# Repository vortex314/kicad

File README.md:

my personal selection of projects and components in Kicad
ESP32
UEXT

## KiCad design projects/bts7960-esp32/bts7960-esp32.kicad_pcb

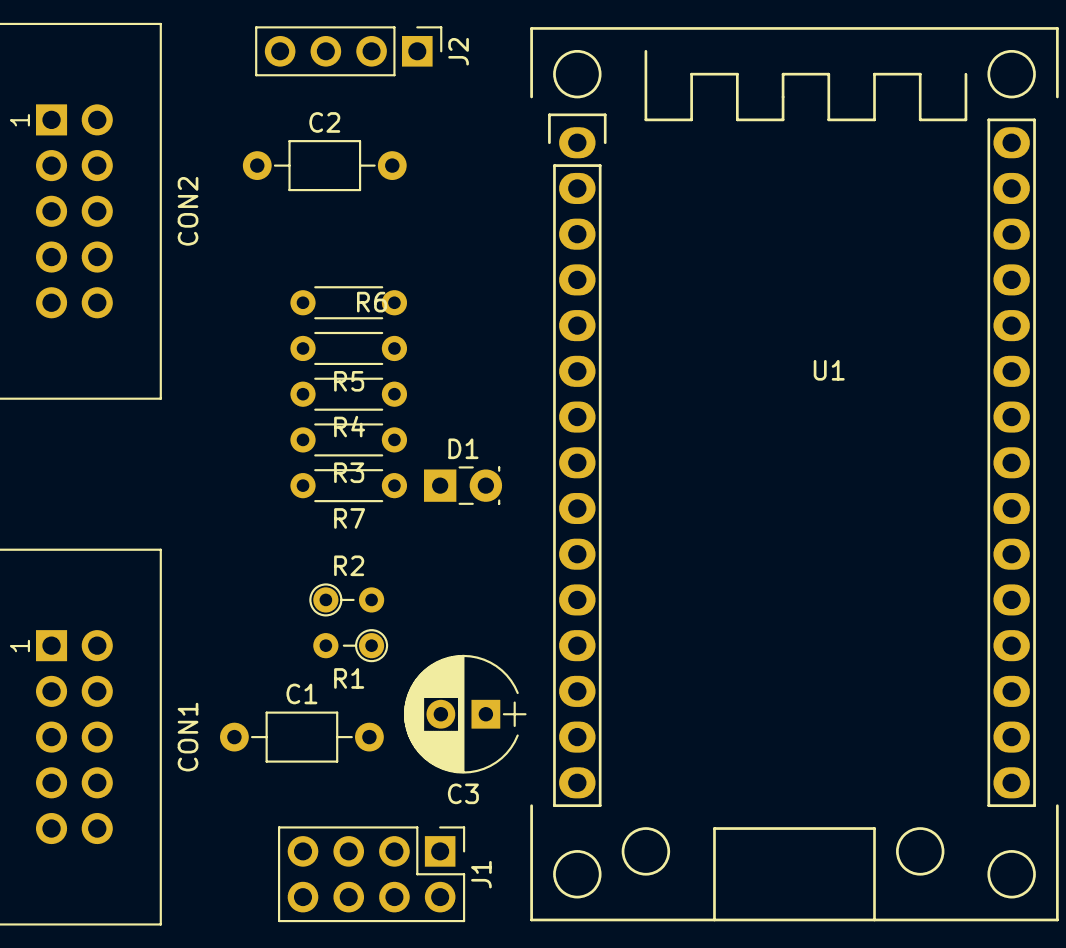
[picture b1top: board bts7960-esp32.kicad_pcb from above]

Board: 2 copper layers, 16 parts (0 on the bottom side), 23 nets, no tracks yet.

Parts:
C1, C2: 0.1µ; C_Axial_L3.8mm_D2.6mm_P7.50mm_Horizontal
C3: CP; CP_Radial_D6.3mm_P2.50mm
CON1, CON2: UEXT-5V; UEXT
D1: LED; LED_Rectangular_W3.9mm_H1.9mm
J1: CONN_02X04; Pin_Header_Straight_2x04_Pitch2.54mm
J2: CONN_01X04; Pin_Header_Straight_1x04_Pitch2.54mm
R1, R2: 10k; R_Axial_DIN0204_L3.6mm_D1.6mm_P2.54mm_Vertical
R3, R4: 10k; R_Axial_DIN0204_L3.6mm_D1.6mm_P5.08mm_Horizontal
R5, R6: 10K; R_Axial_DIN0204_L3.6mm_D1.6mm_P5.08mm_Horizontal
R7: R; R_Axial_DIN0204_L3.6mm_D1.6mm_P5.08mm_Horizontal
U1: ESP32-DEVKIT-V1

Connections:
5V: C3.1, CON1.+5V, CON2.+5V, J1.2, J2.4, R5.1, R6.1, R7.2, U1.15
CHAN_A: CON1.MISO, R4.1, U1.4
CHAN_B: CON2.MISO, R3.1, U1.5
GND: C1.2, C3.2, CON1.GND, CON2.GND, J1.1, J2.1, U1.14, U1.17
L_EN: CON1.SCL, J1.5, U1.8
L_IS: C1.1, R1.2, U1.2
L_PWM: CON1.SSEL, J1.7, U1.6
MOSI1: CON1.MOSI, U1.30
MOSI2: CON2.MOSI, U1.29
unnamed: D1.1, R7.1
unnamed: J1.3, R1.1
unnamed: J1.4, R2.2
unnamed: J2.2, R4.2, R6.2
unnamed: J2.3, R3.2, R5.2
RXD2: C2.1, CON2.RXD, R2.1, U1.3
R_EN: CON1.SDA, J1.6, U1.9
R_PWM: CON2.SSEL, J1.8, U1.7
SCK1: CON1.SCK, U1.22
SCK2: CON2.SCK, U1.21
SCL2: CON2.SCL, U1.10
SDA2: CON2.SDA, U1.11
TXD1: CON1.TXD, U1.25
TXD2: CON2.TXD, U1.24

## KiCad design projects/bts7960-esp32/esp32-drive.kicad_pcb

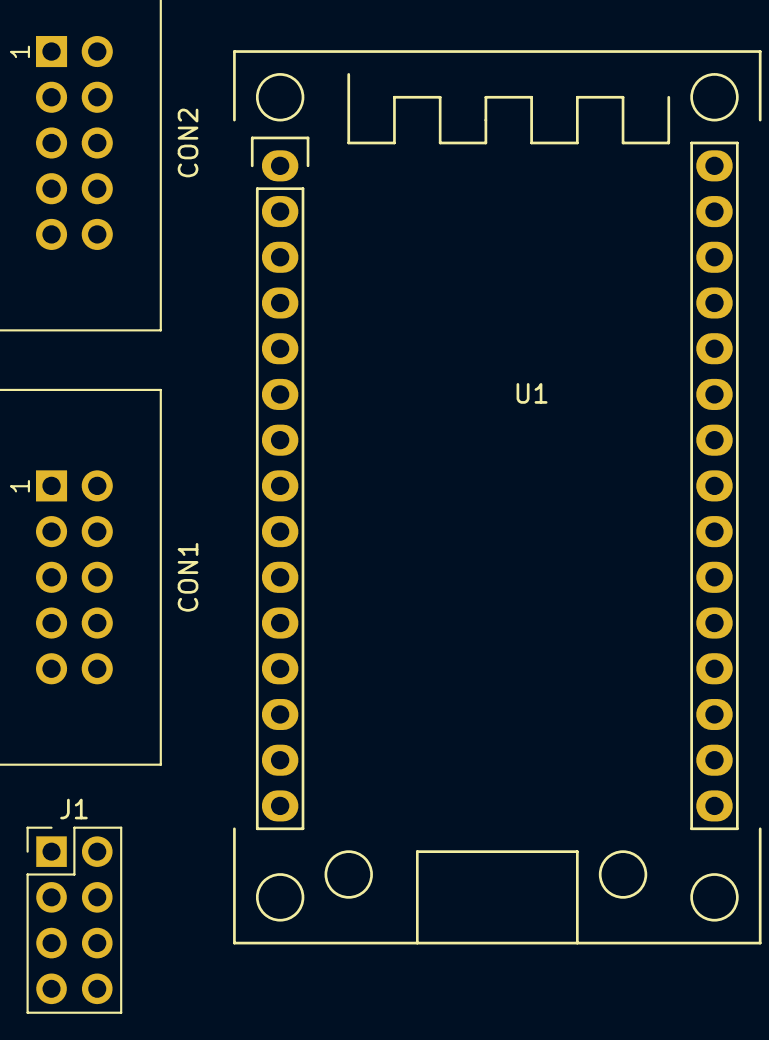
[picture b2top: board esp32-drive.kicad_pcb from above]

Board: 2 copper layers, 4 parts (0 on the bottom side), 18 nets, no tracks yet.

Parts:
CON1, CON2: UEXT
J1: CONN_02X04; Pin_Header_Straight_2x04_Pitch2.54mm
U1: ESP32-DEVKIT-V1

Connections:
5V: J1.2, U1.15
GND: CON1.GND, CON2.GND, J1.1, U1.14, U1.17
MISO1: CON1.MISO, J1.4, U1.4
MISO2: CON2.MISO, U1.5
MOSI1: CON1.MOSI, U1.29
MOSI2: CON2.MOSI, U1.30
RXD1: CON1.RXD, J1.3, U1.2
RXD2: CON2.RXD, U1.3
SCK1: CON1.SCK, U1.21
SCK2: CON2.SCK, U1.22
SCL1: CON1.SCL, J1.5, U1.8
SCL2: CON2.SCL, U1.10
SDA1: CON1.SDA, J1.6, U1.9
SDA2: CON2.SDA, U1.11
SSEL1: CON1.SSEL, J1.8, U1.7
SSEL2: CON2.SSEL, U1.6
TXD1: CON1.TXD, J1.7, U1.25
TXD2: CON2.TXD, U1.24

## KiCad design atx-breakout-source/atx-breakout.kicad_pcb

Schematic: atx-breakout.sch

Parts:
D1: LED_SB; LED-5MM
D2: LED_SW; LED-5MM
D3: LED_OK; LED-5MM
F1, F2, F3, F4, F5, F6: PTC 1.25A; C_1812_HandSoldering
J1: ATX_24PIN; Molex_MiniFit-JR-5556-24A_2x12x4.20mm_Straight
J2, J3: ATX_EPS12V; Molex_MiniFit-JR-5556-08A_2x04x4.20mm_Straight
J4, J5, J6, J7: ATX_PCIE_6PIN; Molex_MiniFit-JR-5556-06A_2x03x4.20mm_Straight_PCIE_6p2
JP1, JP2, JP3: JUMPER3; GND_JMP
JP4: JUMPER; 12V_JMP
P1, P2: CONN_01X01; SolderWirePad_single_0-8mmDrill
P3: CONN_MISC; Socket_Strip_Straight_2x08
P4: CONN_12V_1; TerminalBlock_Pheonix_PT-5.0mm_6pol
P5: CONN_12V_2; TerminalBlock_Pheonix_PT-5.0mm_6pol
P6: CONN_3V3; TerminalBlock_Pheonix_PT-5.0mm_4pol
P7: CONN_5V; TerminalBlock_Pheonix_PT-5.0mm_4pol
R1, R2, R3: 470; Resistor_Horizontal_RM10mm
SW1: SPDT; SW_SPDT_OS102011MS2Q
U1: LOGIC_BUFFER_3ST; SOT-23-5

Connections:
+3V3: F4.2, J1.1 (+3.3V), J1.2 (+3.3V), J1.12 (+3.3V), J1.13 (+3.3V), P6.2, P6.4
+5V: F5.2, J1.4 (+5V), J1.6 (+5V), J1.21 (+5V), J1.22 (+5V), J1.23 (+5V), P7.1, P7.3
+5VSB: D1.2 (A), D2.2 (A), F1.2, J1.9 (+5VSB), U1.5 (VCC)
+12V: F6.2, J1.10 (+12V1), J1.11 (+12V1), J2.5 (+12V), J2.6 (+12V), J2.7 (+12V), J2.8 (+12V), J3.5 (+12V), J3.6 (+12V), J3.7 (+12V), J3.8 (+12V), J4.1 (+12V), J4.2 (+12V), J4.3 (+12V), J5.1 (+12V), J5.2 (+12V), J5.3 (+12V), J6.1 (+12V), J6.2 (+12V), J6.3 (+12V), J7.1 (+12V), J7.2 (+12V), J7.3 (+12V), JP4.1, JP4.2, P4.2, P4.4, P4.6, P5.1, P5.3, P5.5
-5V: F3.2, J1.20 (-5V?)
-12V: F2.2, J1.14 (-12V)
GND: J1.3 (COM), J1.5 (COM), J1.7 (COM), J1.15 (COM), J1.17 (COM), J1.18 (COM), J1.19 (COM), J1.24 (COM), J2.1 (GND), J2.2 (GND), J2.3 (GND), J2.4 (GND), J3.1 (GND), J3.2 (GND), J3.3 (GND), J3.4 (GND), J4.4 (GND), J4.5 (GND), J4.6 (GND), J5.4 (GND), J5.5 (GND), J5.6 (GND), J6.4 (GND), J6.5 (GND), J6.6 (GND), J7.4 (GND), J7.5 (GND), J7.6 (GND), JP1.1, JP1.2, JP1.3, JP2.1, JP2.2, JP2.3, JP3.1, JP3.2, JP3.3, P3.2, P3.4, P3.6, P3.8, P3.10, P3.12, P3.14, P3.16, P4.1, P4.3, P4.5, P5.2, P5.4, P5.6, P6.1, P6.3, P7.2, P7.4, R1.1, R3.1, SW1.2, SW1.3, U1.1 (~OE), U1.3 (GND)
unnamed: D1.1 (K), R1.2
unnamed: D2.1 (K), R2.2
unnamed: D3.1 (K), R3.2
unnamed: F1.1, P3.15
unnamed: F2.1, P3.9
unnamed: F3.1, P3.7
unnamed: F4.1, P3.5
unnamed: F5.1, P3.3
unnamed: F6.1, P3.1
PS_ON: J1.16 (PS_ON), P3.13, R2.1, SW1.1
PWR_OK_BUF: D3.2 (A), P2.1, P3.11, U1.4 (Y)
PWR_OK_RAW: J1.8 (PWROK), P1.1, U1.2 (A)

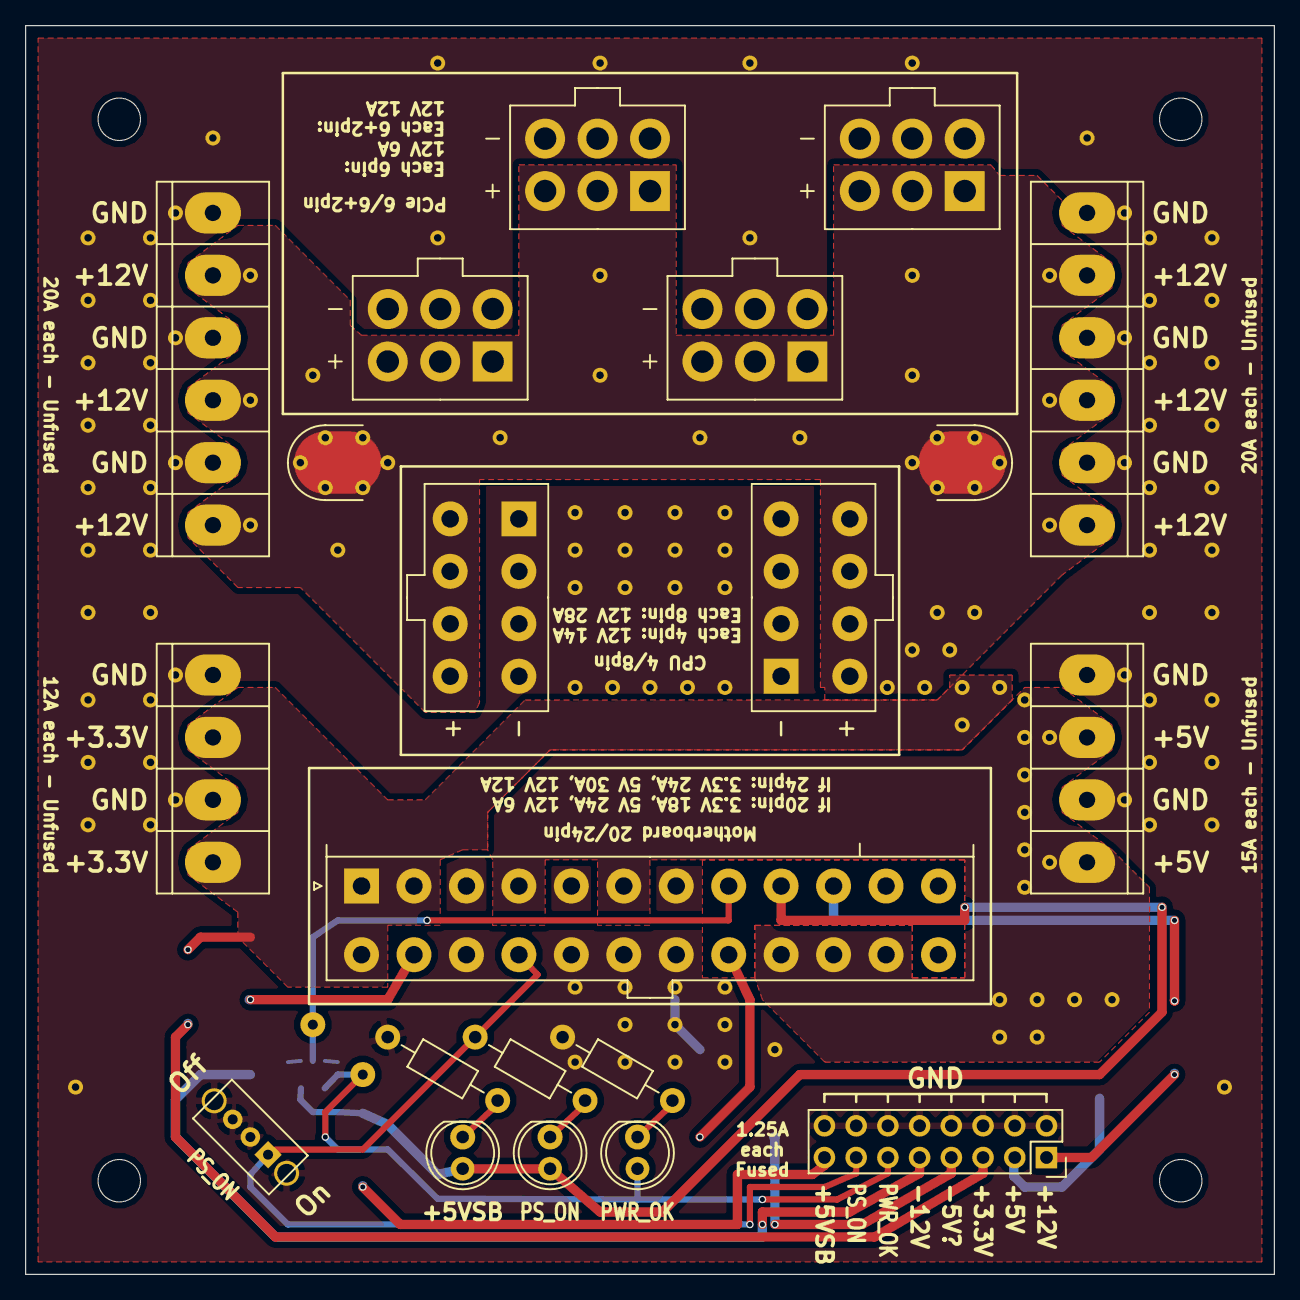
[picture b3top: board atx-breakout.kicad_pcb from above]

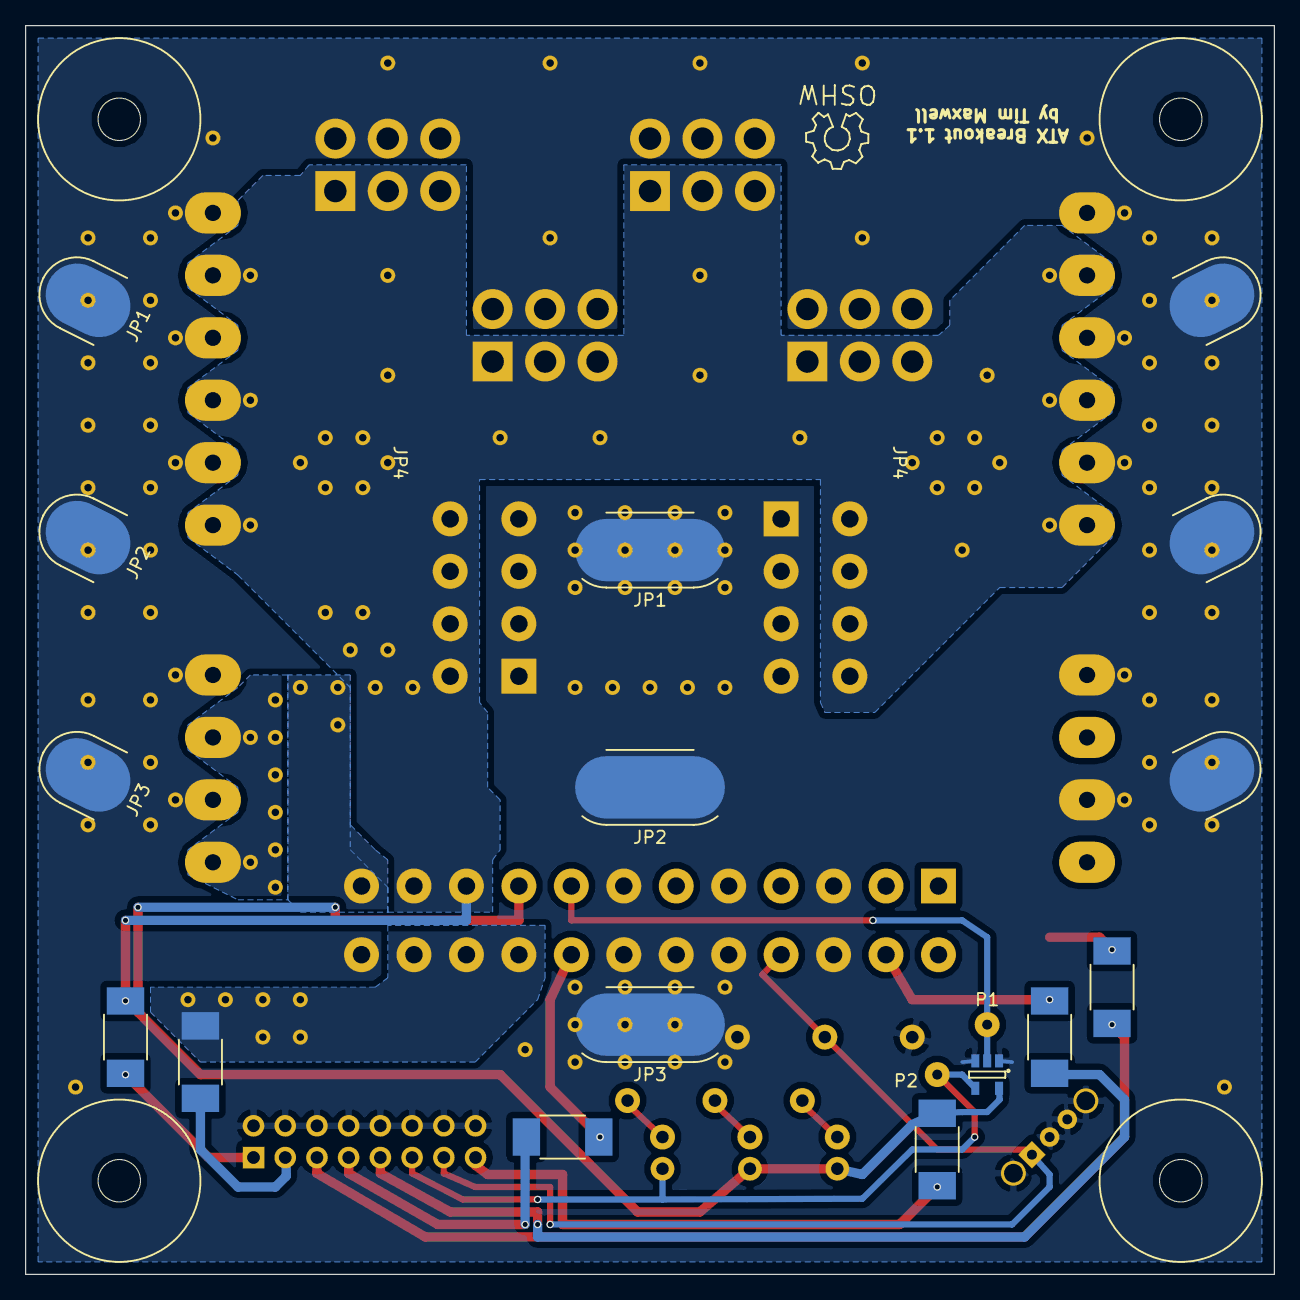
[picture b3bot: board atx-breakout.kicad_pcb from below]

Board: 2 copper layers, 100.0 x 100.0 mm, 36 parts (16 on the bottom side), 19 nets.

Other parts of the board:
BUMPER1, BUMPER2, BUMPER3, BUMPER4: BUMPER

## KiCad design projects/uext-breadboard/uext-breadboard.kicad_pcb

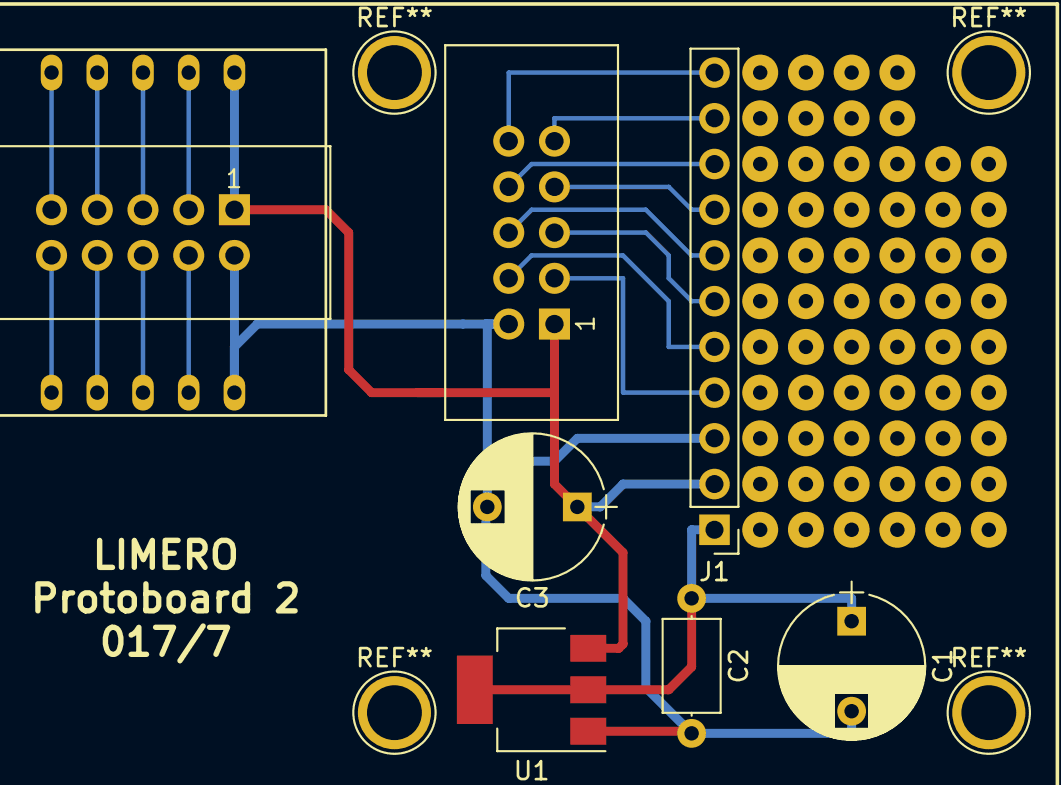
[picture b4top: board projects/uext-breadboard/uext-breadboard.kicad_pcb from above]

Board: 2 copper layers, 5 parts (0 on the bottom side), 3 nets.

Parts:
C1, C3: CP; CP_Radial_D8.0mm_P5.00mm
C2: C; C_Axial_L5.1mm_D3.1mm_P7.50mm_Horizontal
J1: Pin_Header_Straight_1x11_Pitch2.54mm
U1: LM1117-3.3; SOT-223

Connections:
+3V3: C1.1, C2.1, J1.1, U1.2, U1.4
+5V: C3.1, J1.2, U1.3
GND: C1.2, C2.2, C3.2, J1.3, U1.1

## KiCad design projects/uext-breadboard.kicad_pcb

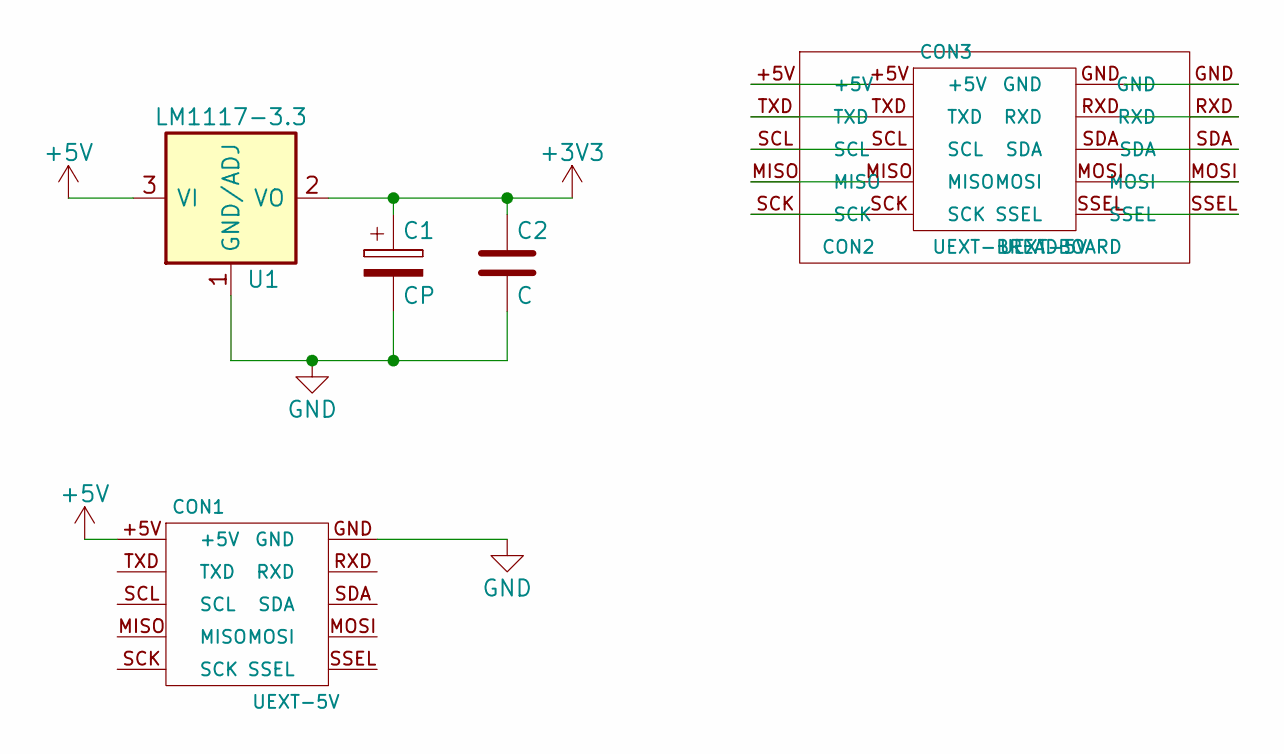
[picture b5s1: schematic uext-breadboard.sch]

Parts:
C1: CP; CP_Axial_L10.0mm_D6.0mm_P15.00mm_Horizontal
C2: C; C_Axial_L5.1mm_D3.1mm_P7.50mm_Horizontal
CON1, CON3: UEXT-5V; UEXT
CON2: UEXT-BREADBOARD
U1: LM1117-3.3; SOT-223

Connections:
+3V3: C1.1, C2.1, U1.2 (VO), U1.4 (VO)
+5V: CON1.+5V, U1.3 (VI)
GND: C1.2, C2.2, CON1.GND, U1.1 (GND/ADJ)
unnamed: CON2.+5V, CON3.+5V
unnamed: CON2.GND, CON3.GND
unnamed: CON2.MISO, CON3.MISO
unnamed: CON2.MOSI, CON3.MOSI
unnamed: CON2.RXD, CON3.RXD
unnamed: CON2.SCK, CON3.SCK
unnamed: CON2.SCL, CON3.SCL
unnamed: CON2.SDA, CON3.SDA
unnamed: CON2.SSEL, CON3.SSEL
unnamed: CON2.TXD, CON3.TXD

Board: 2 copper layers, 6 parts (0 on the bottom side), 13 nets, no tracks yet.

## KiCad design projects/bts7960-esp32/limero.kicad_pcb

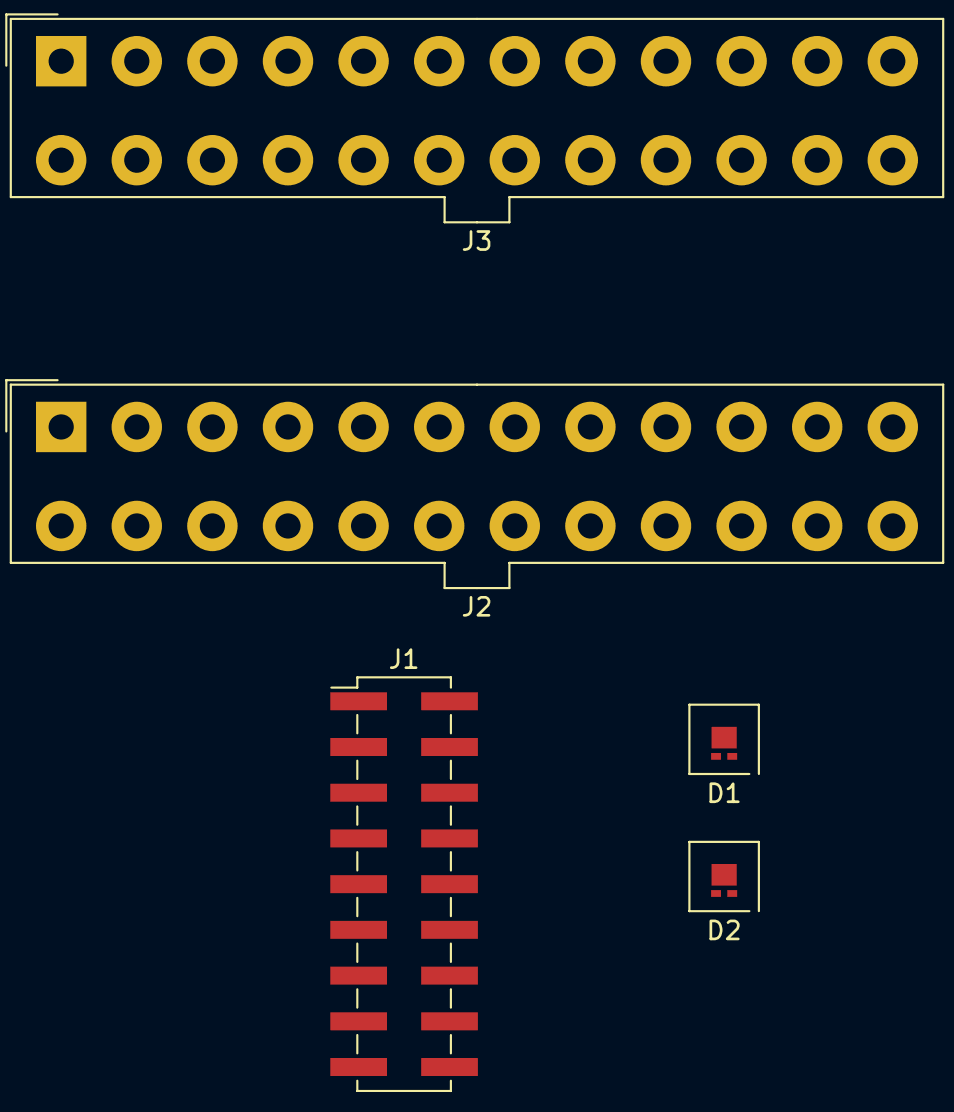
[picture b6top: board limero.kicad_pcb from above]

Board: 2 copper layers, 5 parts (0 on the bottom side), 2 nets, no tracks yet.

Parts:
D1, D2: LED; LED-L1T2_LUMILEDS
J1: CONN_02X09; Pin_Header_Straight_2x09_Pitch2.54mm_SMD
J2: ATX24; Molex_MiniFit-JR-5556-24A_2x12x4.20mm_Straight
J3: ATX_24PIN; Molex_MiniFit-JR-5556-24A_2x12x4.20mm_Straight

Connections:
GND: J2.3, J2.5, J2.7, J2.15, J2.17, J2.18, J2.19, J2.24
unnamed: J1.16, J2.1, J3.1

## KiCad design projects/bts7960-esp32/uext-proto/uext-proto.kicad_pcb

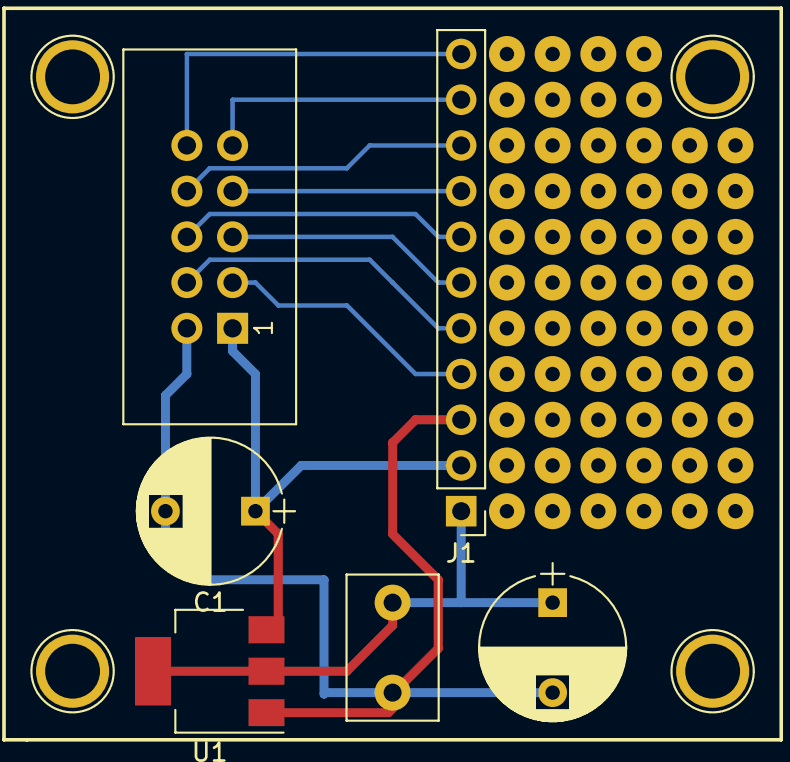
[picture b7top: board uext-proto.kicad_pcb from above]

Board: 2 copper layers, 3 parts (0 on the bottom side), 3 nets.

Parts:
C1: CP; CP_Radial_D8.0mm_P5.00mm
J1: Pin_Header_Straight_1x11_Pitch2.54mm
U1: LM1117-3.3; SOT-223

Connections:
+3V3: J1.1, U1.2, U1.4
+5V: C1.1, J1.2, U1.3
GND: C1.2, J1.3, U1.1

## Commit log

2017-07-20 starting
2017-07-21 added latest projects
2017-07-22 made proto board for UEXT connector
2018-04-29 working...
2018-04-29 working on atx connector board
2018-05-13 working on lawnmower
2018-05-13 added some
2018-05-13 working on bts7960 drive
2018-06-06 working on universal esp32 board
